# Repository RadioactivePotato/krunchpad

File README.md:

# krunchpad
A macropad powered by RP2040

# Images

| Schematic | PCB | 3D Preview | Case |
|:---------:|:---:|:----:|:----:|
|  |  |  |  |
| | |  | |

# Case

| Layout | Layout | Layout |
| :----: | :----: | :----: |
|  |  |  |

# BOM
| Qty  | Item                               | Notes                     | Cost (USD)| URL     |
|------|------------------------------------|---------------------------|-----------|---------|
| 1    | Seeed Studio XIAO RP2040           | Microcontroller           | $4.68     | [URL](https://www.digikey.co.uk/en/products/detail/seeed-technology-co-ltd/102010428/14672129) |
| 12   | THT 1N4148 Diode (DO-35 Footprint) | For switch matrix         | $0.41     | [URL](https://www.digikey.co.uk/en/products/detail/diotec-semiconductor/1N4148/13164514) |
| 12   | MX-Style Switches                  | Mechanical key switches   |           |         |
| 1    | EC11 Rotary Encoder                | Volume control            | $1.87     | [URL](https://www.digikey.co.uk/en/products/detail/bourns-inc/PEC11R-4215K-S0012/4499639) |
| 1    | 0.91" OLED Display                 |                           |           |         |
| 12   | Keycaps                            |                           |           |         |
| 5    | M3x5mmx4mm Heatset Inserts (W*H)   | For mounting              |           |         |
| 6    | M3 Screws (5.6mm Max)              | For case assembly         |           |         |
|------|------------------------------------|---------------------------|-----------|---------|
| 1    | Soldering Iron + Solder            | Tools                     |           |         |
| 1    | 3D Printed Case                    | Custom enclosure          |           |         |
| 1    | PCB                                |                           |           |         |
|------|------------------------------------|---------------------------|-----------|---------|
| 2    | 2.54mm 4POS Header (Included)      | OLED Mounting             |           |         |
| 2    | 2.54mm 4POS Socket                 | OLED Mounting             | $0.25     | [URL](https://www.digikey.co.uk/en/products/detail/adam-tech/RS1-04-G/9829303) |
| 2    | 2.54mm 7POS Header                 | MCU Mounting              | $0.20     | [URL](https://www.digikey.co.uk/en/products/detail/adam-tech/PH1-07-UA/9830505) |
| 2    | 2.54mm 7POS Socket                 | MCU Mounting              | $0.84     | [URL](https://www.digikey.co.uk/en/products/detail/adam-tech/RS1-07-G/9832045) |
| 12   | Kailh MX Hotswap Socket (Optional) | Hotswapping for switches  | $4.95     | [URL](https://www.digikey.co.uk/en/products/detail/adafruit-industries-llc/4958/13997772) |
|------|------------------------------------|---------------------------|-----------|---------|

# Cases
- V1

Simple base plate with slots for heatset inserts

- V1.1

Added holes for the PCB to sit flush with the case where there are THT componants

- V1.2

Added a support knob to support the PCB in the center of the case

- V1.3

Added slots for the socket for the MCU

Removed the curved corners for the holes

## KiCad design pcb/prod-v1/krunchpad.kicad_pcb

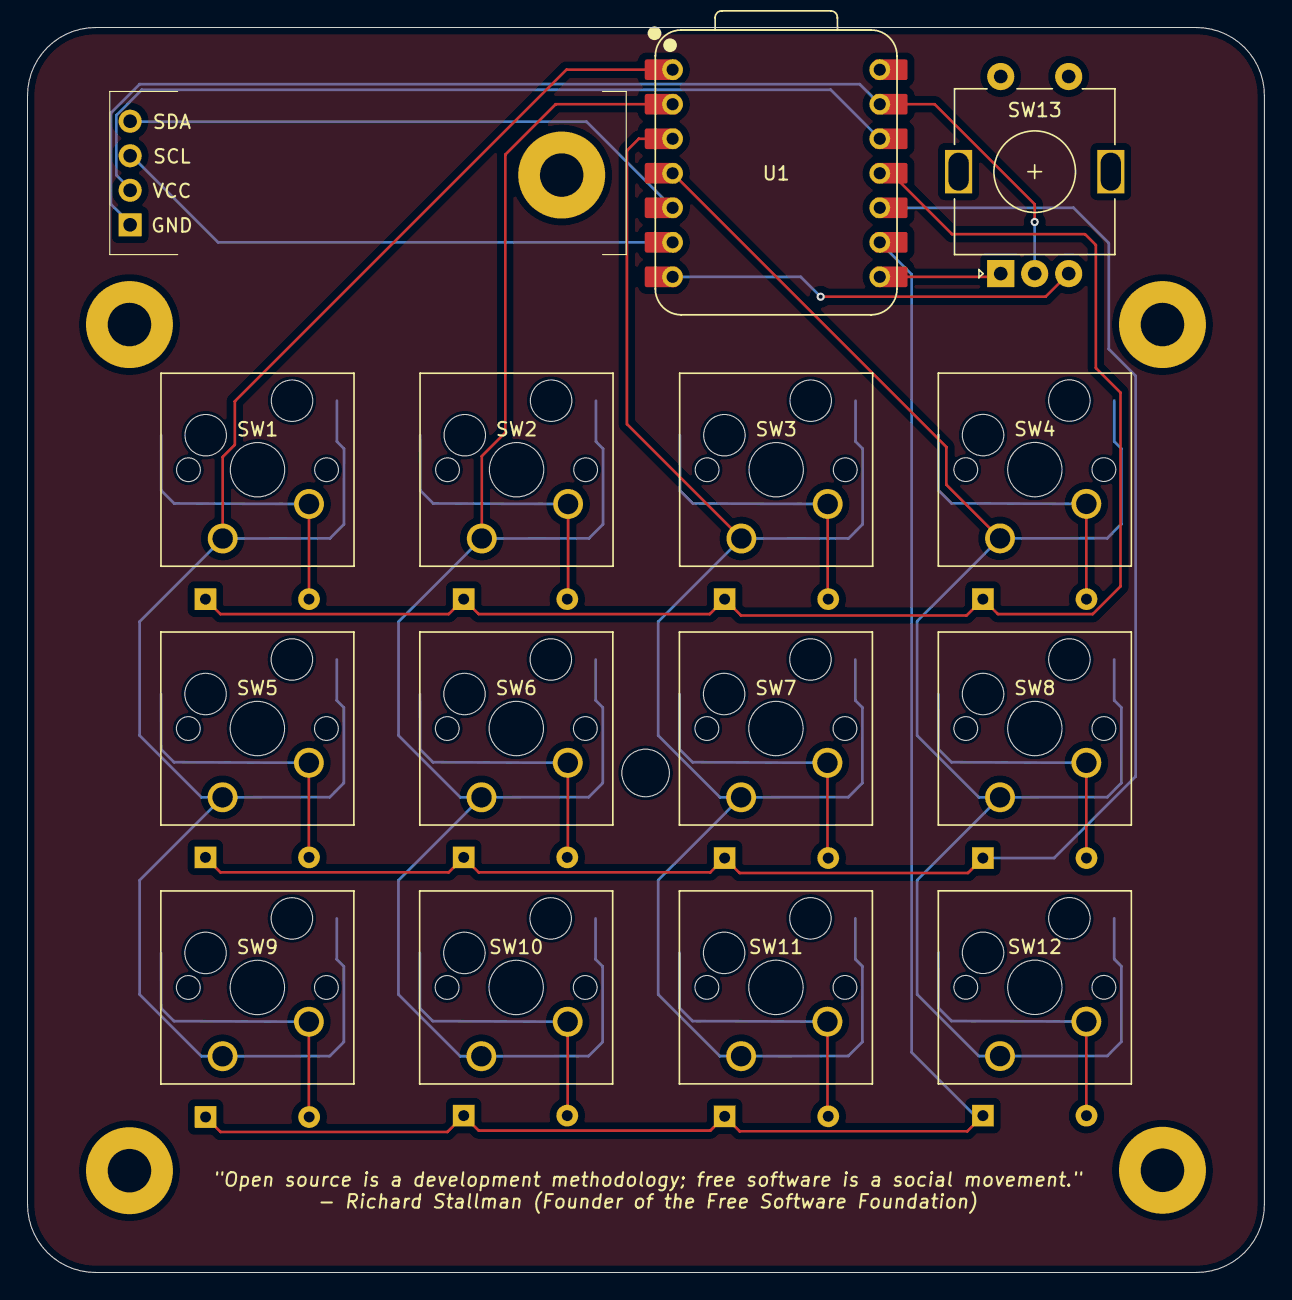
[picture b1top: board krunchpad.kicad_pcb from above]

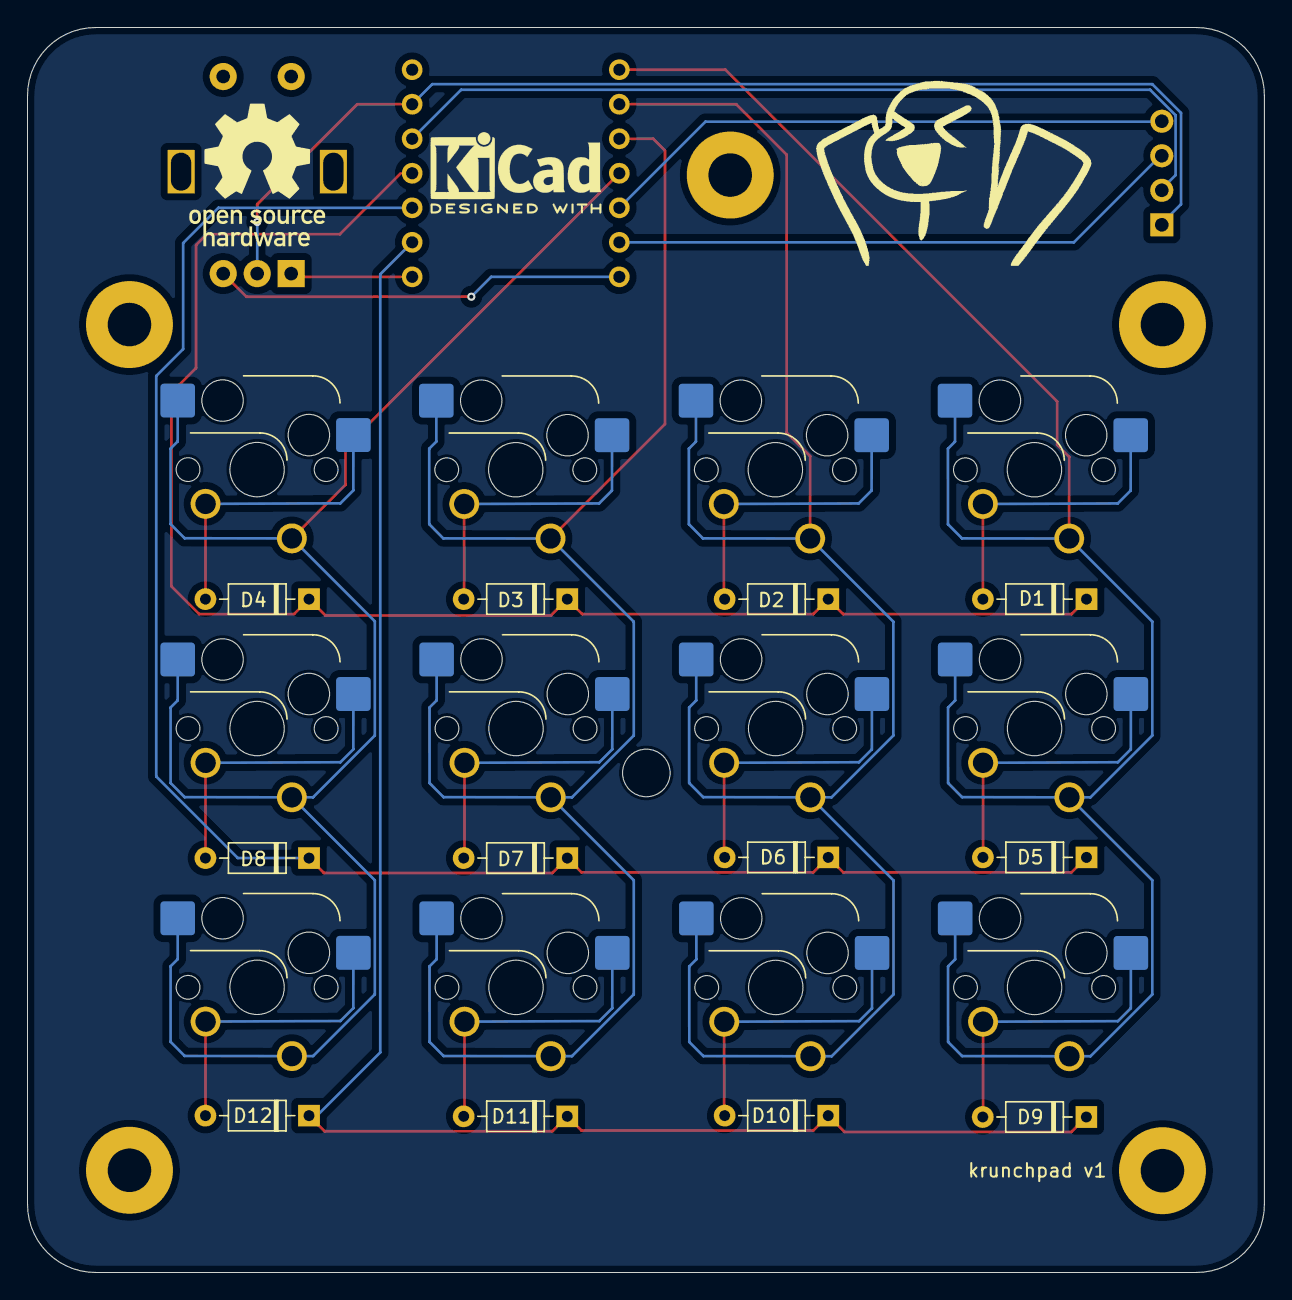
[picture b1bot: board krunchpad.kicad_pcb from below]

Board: 2 copper layers, 91.0 x 91.6 mm, 28 parts (13 on the bottom side), 25 nets.

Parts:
D1, D2, D3, D4, D5, D6, D7, D8, D9, D10, D11, D12: 1N4148; D_DO-35_SOD27_P7.62mm_Horizontal
J1: OLED_128x32; SSD1306-0.91-OLED-4pin-128x32
SW1, SW2, SW3, SW4, SW5, SW6, SW7, SW8, SW9, SW10, SW11, SW12: SW_Push_45deg; dual-hotswap_MX
SW13: RotaryEncoder_Switch; RotaryEncoder_Alps_EC11E-Switch_Vertical_H20mm
U1: XIAO-RP2040-DIP
logo1: KiCad-Logo2_5mm_SilkScreen

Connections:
+3V3: J1.2 (VCC), U1.12 (3V3)
C1: SW1.1, SW5.1, SW9.1, U1.1 (GPIO26/ADC0/A0)
C2: SW2.1, SW6.1, SW10.1, U1.2 (GPIO27/ADC1/A1)
C3: SW3.1, SW7.1, SW11.1, U1.3 (GPIO28/ADC2/A2)
C4: SW4.1, SW8.1, SW12.1, U1.4 (GPIO29/ADC3/A3)
GND: J1.1 (GND), SW13.C, U1.13 (GND)
GPIO0: SW13.B, U1.7 (GPIO0/TX)
GPIO1: SW13.A, U1.8 (GPIO1/RX)
unnamed: D1.2 (A), SW1.2
unnamed: D2.2 (A), SW2.2
unnamed: D3.2 (A), SW3.2
unnamed: D4.2 (A), SW4.2
unnamed: D5.2 (A), SW5.2
unnamed: D6.2 (A), SW6.2
unnamed: D7.2 (A), SW7.2
unnamed: D8.2 (A), SW8.2
unnamed: D9.2 (A), SW9.2
unnamed: D10.2 (A), SW10.2
unnamed: D11.2 (A), SW11.2
unnamed: D12.2 (A), SW12.2
unnamed: J1.3 (SCL), U1.6 (GPIO7/SCL)
unnamed: J1.4 (SDA), U1.5 (GPIO6/SDA)
R1: D1.1 (K), D2.1 (K), D3.1 (K), D4.1 (K), U1.11 (GPIO3/MOSI)
R2: D5.1 (K), D6.1 (K), D7.1 (K), D8.1 (K), U1.10 (GPIO4/MISO)
R3: D9.1 (K), D10.1 (K), D11.1 (K), D12.1 (K), U1.9 (GPIO2/SCK)

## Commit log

2025-06-07 ship
2025-06-07 added images to readme
2025-06-07 case layout
2025-06-07 updated case model and image
2025-06-07 changed case image
2025-06-07 readme case image
2025-06-07 case v1.2
2025-06-07 case v1.2 image
2025-06-08 license
2025-06-09 Update BOM
2025-06-12 deleted old files
2025-06-12 added silkscreen stuff, and copper fill
2025-06-15 case v1.3
2025-06-15 readme case v1.3 image
2025-06-16 Updated bill of materials for OLED and MCU mounting
2025-06-21 updated bom values
2025-06-21 added urls to bom
2025-06-26 removed old pcb designed files to be replaced with new ones
2025-06-26 final v1 files
2025-07-23 updated code to make oled work, +non functional neopixel, fixed pin names
